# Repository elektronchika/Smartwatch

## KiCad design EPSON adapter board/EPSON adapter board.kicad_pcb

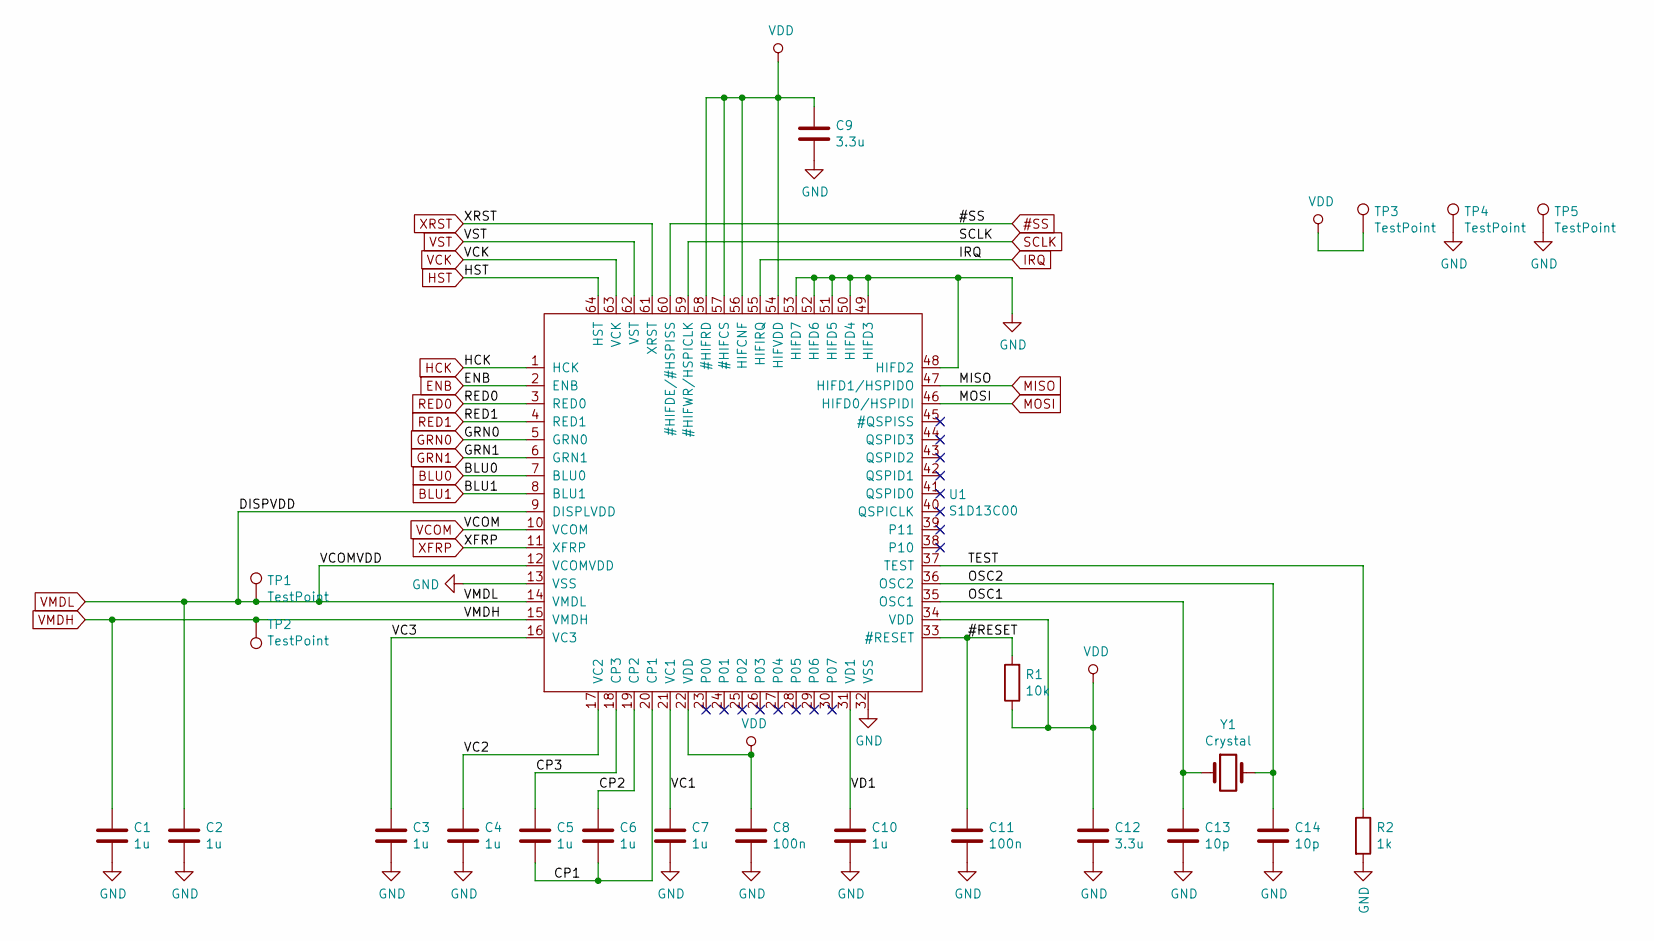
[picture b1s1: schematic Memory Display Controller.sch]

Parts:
C1, C2, C3, C4, C5, C6, C7, C10: 1u; C_0603_1608Metric
C8, C11: 100n; C_0603_1608Metric
C9, C12: 3.3u; C_0603_1608Metric
C13, C14: 10p; C_0603_1608Metric
R1: 10k; R_0603_1608Metric
R2: 1k; R_0603_1608Metric
TP1, TP2, TP3, TP4, TP5: TestPoint; Pin_D1.0mm_L10.0mm
U1: S1D13C00; LQFP-64_10x10mm_P0.5mm
Y1: Crystal; Crystal_SMD_3215-2Pin_3.2x1.5mm

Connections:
#SS: U1.60 (#HIFDE/#HSPISS); also elsewhere on the board
/Memory Display Controller/#RESET: C11.1, R1.2, U1.33 (#RESET)
/Memory Display Controller/CP1: C5.2, C6.2, U1.20 (CP1)
/Memory Display Controller/CP2: C6.1, U1.19 (CP2)
/Memory Display Controller/CP3: C5.1, U1.18 (CP3)
/Memory Display Controller/OSC1: C13.1, U1.35 (OSC1), Y1.1
/Memory Display Controller/OSC2: C14.1, U1.36 (OSC2), Y1.2
/Memory Display Controller/TEST: R2.1, U1.37 (TEST)
/Memory Display Controller/VC1: C7.1, U1.21 (VC1)
/Memory Display Controller/VC2: C4.1, U1.17 (VC2)
/Memory Display Controller/VC3: C3.1, U1.16 (VC3)
/Memory Display Controller/VD1: C10.1, U1.31 (VD1)
BLU0: U1.7 (BLU0); also elsewhere on the board
BLU1: U1.8 (BLU1); also elsewhere on the board
ENB: U1.2 (ENB); also elsewhere on the board
GND: C1.2, C2.2, C3.2, C4.2, C7.2, C8.2, C9.2, C10.2, C11.2, C12.2, C13.2, C14.2, R2.2, TP4.1, TP5.1, U1.13 (VSS), U1.32 (VSS), U1.48 (HIFD2), U1.49 (HIFD3), U1.50 (HIFD4), U1.51 (HIFD5), U1.52 (HIFD6), U1.53 (HIFD7); also elsewhere on the board
GRN0: U1.5 (GRN0); also elsewhere on the board
GRN1: U1.6 (GRN1); also elsewhere on the board
HCK: U1.1 (HCK); also elsewhere on the board
HST: U1.64 (HST); also elsewhere on the board
IRQ: U1.55 (HIFIRQ); also elsewhere on the board
MISO: U1.47 (HIFD1/HSPIDO); also elsewhere on the board
MOSI: U1.46 (HIFD0/HSPIDI); also elsewhere on the board
RED0: U1.3 (RED0); also elsewhere on the board
RED1: U1.4 (RED1); also elsewhere on the board
SCLK: U1.59 (#HIFWR/HSPICLK); also elsewhere on the board
VCK: U1.63 (VCK); also elsewhere on the board
VCOM: U1.10 (VCOM); also elsewhere on the board
VDD: C8.1, C9.1, C12.1, R1.1, TP3.1, U1.22 (VDD), U1.34 (VDD), U1.54 (HIFVDD), U1.56 (HIFCNF), U1.57 (#HIFCS), U1.58 (#HIFRD); also elsewhere on the board
VMDH: C1.1, TP2.1, U1.15 (VMDH); also elsewhere on the board
VMDL: C2.1, TP1.1, U1.9 (DISPLVDD), U1.12 (VCOMVDD), U1.14 (VMDL); also elsewhere on the board
VST: U1.62 (VST); also elsewhere on the board
XFRP: U1.11 (XFRP); also elsewhere on the board
XRST: U1.61 (XRST); also elsewhere on the board

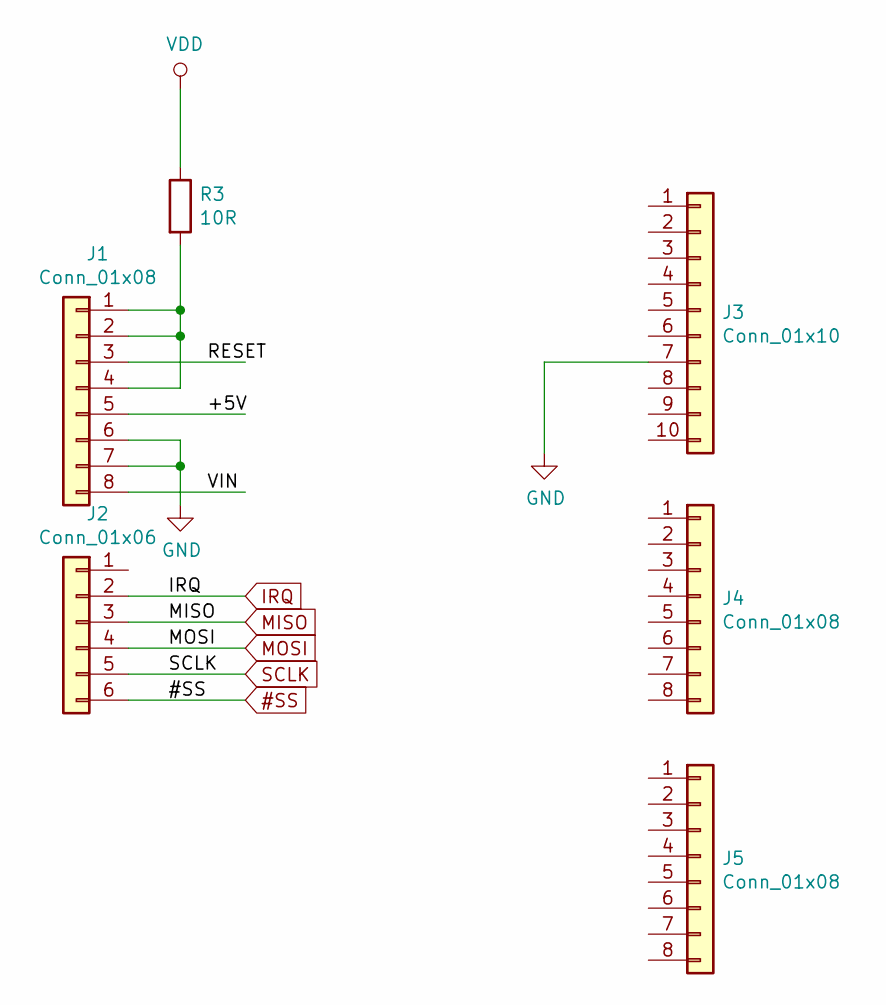
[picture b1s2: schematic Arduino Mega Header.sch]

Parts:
J1, J4, J5: Conn_01x08; PinHeader_1x08_P2.54mm_Vertical
J2: Conn_01x06; PinHeader_1x06_P2.54mm_Vertical
J3: Conn_01x10; PinHeader_1x10_P2.54mm_Vertical
R3: 10R; R_0603_1608Metric

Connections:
#SS: J2.6; also elsewhere on the board
/Arduino Mega Header/+5V: J1.5
/Arduino Mega Header/RESET: J1.3
/Arduino Mega Header/VIN: J1.8
GND: J1.6, J1.7, J3.7; also elsewhere on the board
IRQ: J2.2; also elsewhere on the board
MISO: J2.3; also elsewhere on the board
MOSI: J2.4; also elsewhere on the board
unnamed: J1.1, J1.2, J1.4, R3.2
SCLK: J2.5; also elsewhere on the board
VDD: R3.1; also elsewhere on the board

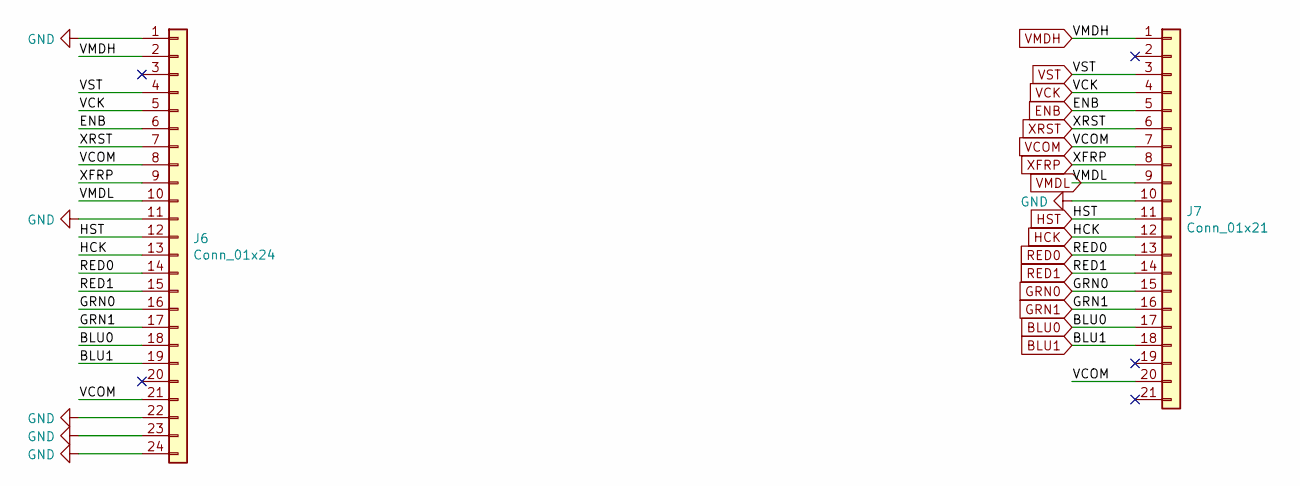
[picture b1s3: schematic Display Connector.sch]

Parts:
J6: Conn_01x24; FH34SRJ-24S-0.5SH(99)
J7: Conn_01x21; Molex-503566-2100

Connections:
BLU0: J6.18, J7.17; also elsewhere on the board
BLU1: J6.19, J7.18; also elsewhere on the board
ENB: J6.6, J7.5; also elsewhere on the board
GND: J6.1, J6.11, J6.22, J6.23, J6.24, J7.10; also elsewhere on the board
GRN0: J6.16, J7.15; also elsewhere on the board
GRN1: J6.17, J7.16; also elsewhere on the board
HCK: J6.13, J7.12; also elsewhere on the board
HST: J6.12, J7.11; also elsewhere on the board
RED0: J6.14, J7.13; also elsewhere on the board
RED1: J6.15, J7.14; also elsewhere on the board
VCK: J6.5, J7.4; also elsewhere on the board
VCOM: J6.8, J6.21, J7.7, J7.20; also elsewhere on the board
VMDH: J6.2, J7.1; also elsewhere on the board
VMDL: J6.10, J7.9; also elsewhere on the board
VST: J6.4, J7.3; also elsewhere on the board
XFRP: J6.9, J7.8; also elsewhere on the board
XRST: J6.7, J7.6; also elsewhere on the board

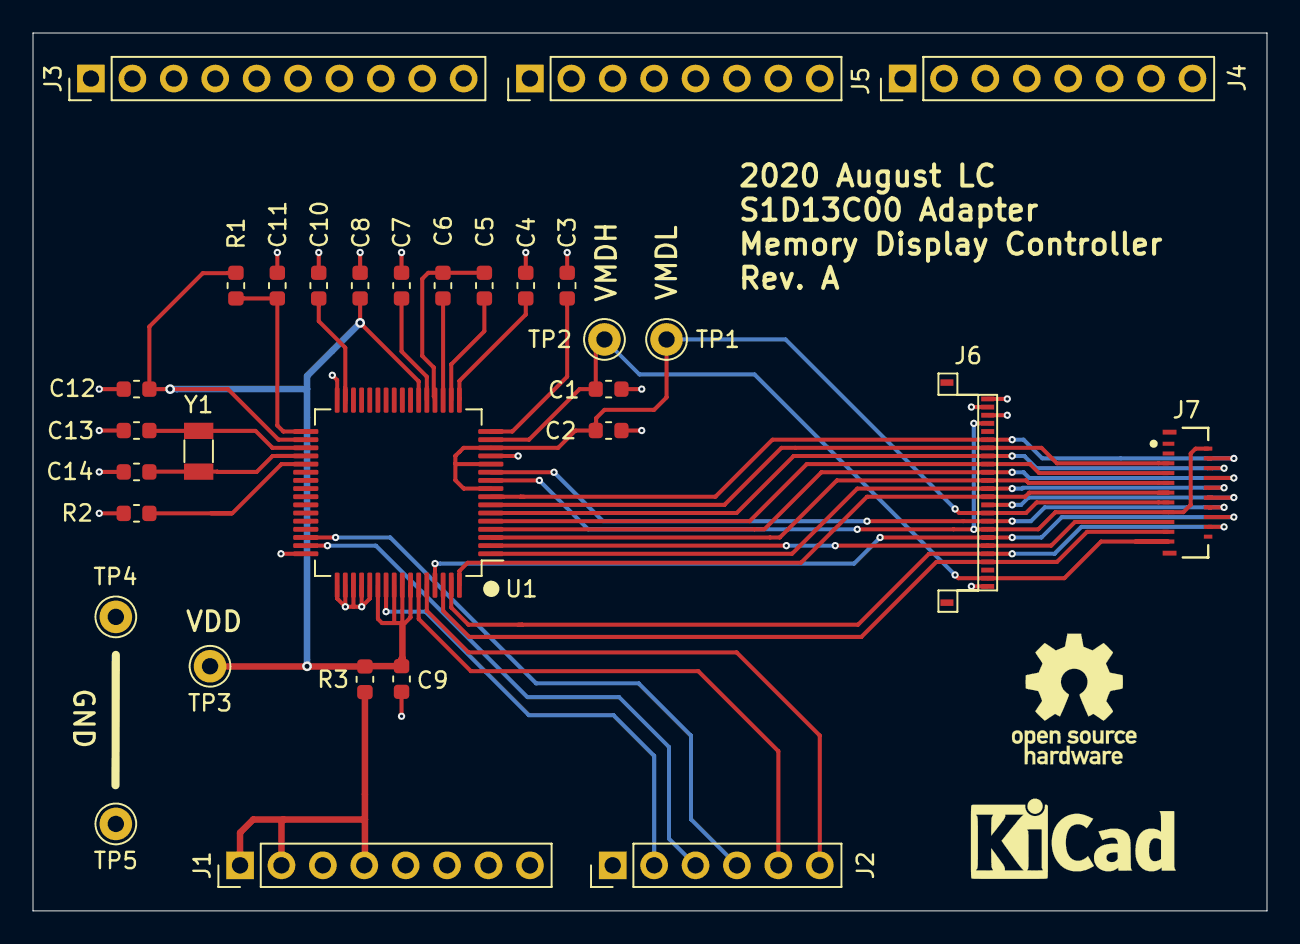
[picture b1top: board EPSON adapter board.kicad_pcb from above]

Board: 2 copper layers, 75.7 x 53.8 mm, 31 parts (0 on the bottom side), 35 nets.

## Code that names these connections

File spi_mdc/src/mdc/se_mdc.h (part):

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
typedef enum {
     seMDC_IOSC             = 0,        ///< IOSC is a CLK source.
     seMDC_OSC1             = 1         ///< OSC1 is a CLK source.
 } seMDC_ClkSrc;

typedef enum {
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} seMDC_DISP_GSPANEL;

typedef enum {
    seMDC_DISP_VCKNORM      = 0,        ///< VCK pulses are normal
    seMDC_DISP_VCKFAST      = 1U        ///< VCK pulses are fast for the lines that are not updated
} seMDC_DISP_FASTVCK;

typedef enum {
    seMDC_DISP_ENBLSB       = 0,        ///< ENB pulses start on first LSB pixel data
    seMDC_DISP_ENBMSB       = 1U        ///< ENB pulses start on first MSB pixel data
} seMDC_DISP_ENBPHASE;

typedef enum {
    seMDC_DISP_HSTFALL      = 0,        ///< HST falling edge is after HCK fall
    seMDC_DISP_HSTRISE      = 1U        ///< HST falling edge is after HCK rise
} seMDC_DISP_HST;

typedef enum {
    seMDC_DISP_VSTFALL      = 0,        ///< VST falling edge is after VCK fall
    seMDC_DISP_VSTRISE      = 1U        ///< VST falling edge is after VCK rise
} seMDC_DISP_VST;

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
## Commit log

2020-06-27 SW 1.8 inch rectangle initial commit
2020-06-28 Added button2 and button3. button2 is used as button4 as well.
2020-06-28 Added buttn2 and button 3
2020-07-02 Size in x and y reduced with 2mm
2020-07-15 Added initial version of the test firmware
2020-07-17 Added LVGL into project.
    lvgl-7.1.0 folder shall be placed in $SDK\external\
2020-07-20 Added clock and date
    using time.h and text area to display it on the display
2020-07-21 Added text area for displaying data sent over BLE
    + added peer manager to the project
2020-07-21 Thinner wall and improved band brackets
2020-07-21 1.2 inch round initial commit
    work in progress
2020-08-10 New design idea for the 1.2 inch round one
2020-08-10 Duplicated
2020-08-10 Improved strap fixing points
2020-08-10 added display step file
2020-08-24 Rev. A initial commit
    An Arduino shield for interfacing S1D13C00 memory display controller
2020-08-24 Added SPI test project for controlling memory display controller
2020-08-25 Fixed spi 8 and 16 bit read
2020-08-25 added pdf schematic

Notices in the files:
spi_mdc/src/mdc/se_mdc.h:
Copyright(C) SEIKO EPSON CORPORATION 2017-2018. All rights reserved.
